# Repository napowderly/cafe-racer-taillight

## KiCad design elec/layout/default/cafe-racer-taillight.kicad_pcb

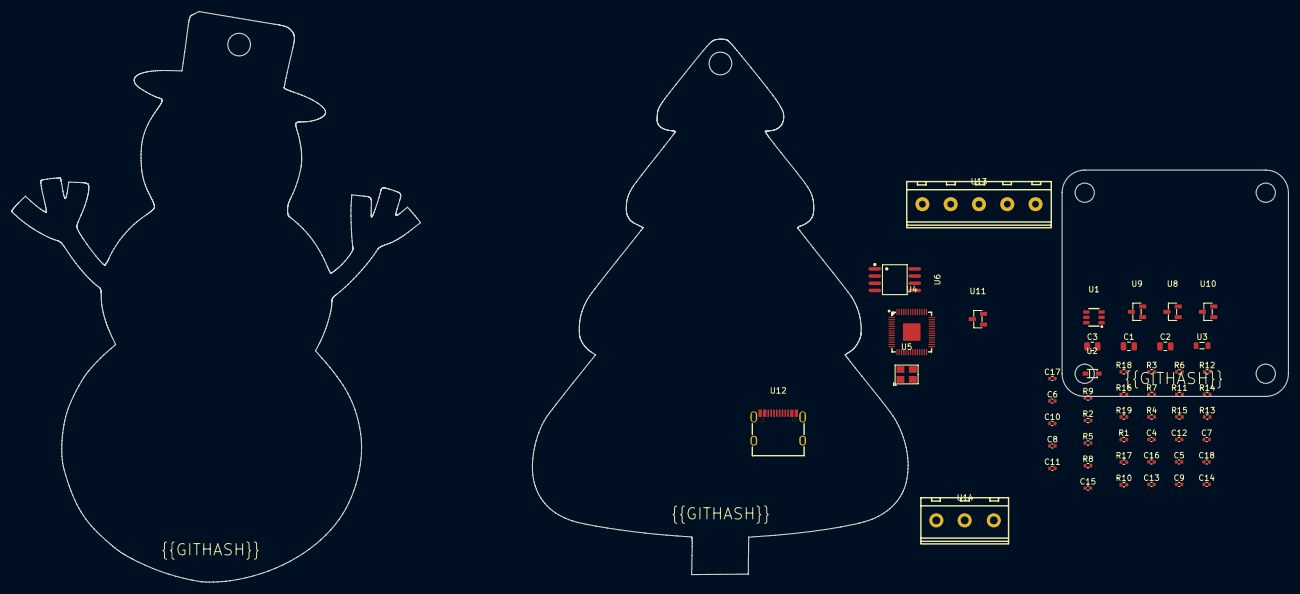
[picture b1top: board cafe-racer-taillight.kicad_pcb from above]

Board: 2 copper layers, 225.7 x 100.8 mm, 50 parts (0 on the bottom side), 35 nets, no tracks yet.

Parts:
C1, C2, C3: 10.0 uF; C0805
C4, C7, C8, C9, C10, C11, C13, C14, C15: 100.0 nF; C0402
C5, C6: 22.0 pF; C0402
C12, C16, C17, C18: 1.0 uF; C0402
R1: 51.0 KΩ; R0402
R2, R6, R7, R9, R10, R11, R12, R13, R14, R15, R16, R17: 10.0 KΩ; R0402
R3: 1.0 KΩ; R0402
R4, R5: 27.0 KΩ; R0402
R8: 18.0 KΩ; R0402
R18, R19: 5.1 KΩ; R0402
U1: SOT-23-6_L2.9-W1.6-P0.95-LS2.8-BR
U2: SOD-323_L1.8-W1.3-LS2.5-RD
U3: L0805
U4: LQFN-56_L7.0-W7.0-P0.4-EP
U5: OSC-SMD_4P-L3.2-W2.5-BL
U6: SOIC-8_L5.3-W5.3-P1.27-LS8.0-BL
U8, U9, U10, U11: SOT-23-3_L2.9-W1.3-P1.90-LS2.4-BR
U12: USB-C-SMD_KH-TYPE-C-16P
U13: CONN-TH_5P-P5.00_WJ127-5.0-5P
U14: CONN-TH_3P-P5.00_WJ127-5.0-3P

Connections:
CC1: R18.1, U12.A5
CC2: R19.1, U12.B5
cs: R7.2, U4.56, U6.1
dm: R5.1, U12.A7, U12.B7
dp: R4.2, U12.A6, U12.B6
gnd-1: C1.2, C17.2, R2.2, R18.2, R19.2, U1.2, U2.2, U12.1, U12.2, U12.3, U12.4, U12.A1, U12.A12, U12.B1, U12.B12, U14.2
gnd-2: C4.2, U1.6, U2.1, U3.1
gnd-5: C5.2, C6.2, C7.2, C8.2, C9.2, C10.2, C11.2, C12.2, C13.2, C14.2, C15.2, C16.2, C18.2, R9.2, U4.19, U4.57, U5.2, U5.4, U6.4
gpio0: R10.2, U4.2, U8.2
gpio1: R12.2, U4.3, U9.2
gpio2: R14.2, U4.4, U10.2
gpio3: R16.2, U4.5, U11.2
hv_signal: R11.2, U8.3, U13.3
hv_signal-1: R13.2, U9.3, U13.4
hv_signal-2: R15.2, U10.3, U13.5
hv_signal-3: R17.2, U11.3, U14.3
io0: U4.53, U6.5
io1: U4.55, U6.2
io2: U4.54, U6.3
io3: U4.51, U6.7
out: R1.2, R2.1, U1.3
out-1: R8.2, R9.1
run: R6.2, U4.26
sck: U4.52, U6.6
usb_dm: R5.2, U4.46
usb_dp: R4.1, U4.47
vcc: R11.1, R13.1, R15.1, U13.1
vcc-1: C1.1, U1.4, U1.5
vcc-2: C17.1, R1.1, R17.1, U3.2, U12.A4, U12.A9, U12.B4, U12.B9, U14.1
vcc-3: C4.1, U1.1
vcc-6: C7.1, C8.1, C9.1, C10.1, C11.1, C12.1, C18.1, R6.1, R7.1, R8.1, R10.1, R12.1, R14.1, R16.1, U4.1, U4.10, U4.22, U4.33, U4.42, U4.43, U4.44, U4.48, U4.49, U6.8, U8.1, U9.1, U10.1, U11.1
vcc-7: C13.1, C14.1, C15.1, C16.1, U4.23, U4.45, U4.50
vcc-8: C5.1, U4.20, U5.1
vcc-9: C6.1, R3.2, U5.3
xout: R3.1, U4.21

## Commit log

2024-01-07 Configure project
2024-01-08 initial design
